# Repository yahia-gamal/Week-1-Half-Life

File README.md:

First, some files are called star, as i intended to make starbie but changed my opinion.

Second, i did a very bad mistake by building up the time until i got to work on this project for 6 hours in a single day and it wasn't the best experience. Luckily, i knew how to deal with KiCad but later on, i won't be able to deal with CADing.

First thing i did in that project was following the project without changing anything 
Those are photos of what i have done.

I followed the tutorial and made the whole star in about 2-2.5 hours
After having some rest, i continued on this project but decided to continue with a bunny instead of star because why not (Idk the reason tbh)

After spending 3 hours on fixing bugs and adding other circuits (I only added LDR and haptic motor), I finished with those. And i admit they were so impressive and i was proud

Spent the rest of the time preparing the code by adding some conditions like forcing sleeping when there is no to little amount of light using LDR and followed the rest of the tutorial. In addition, i added my rabbit pet instead of the pet that was provided in the tutorial.
Finally, i set up github to publish this and future projects.
(i know git was supposed to be done first, but it is what it is)

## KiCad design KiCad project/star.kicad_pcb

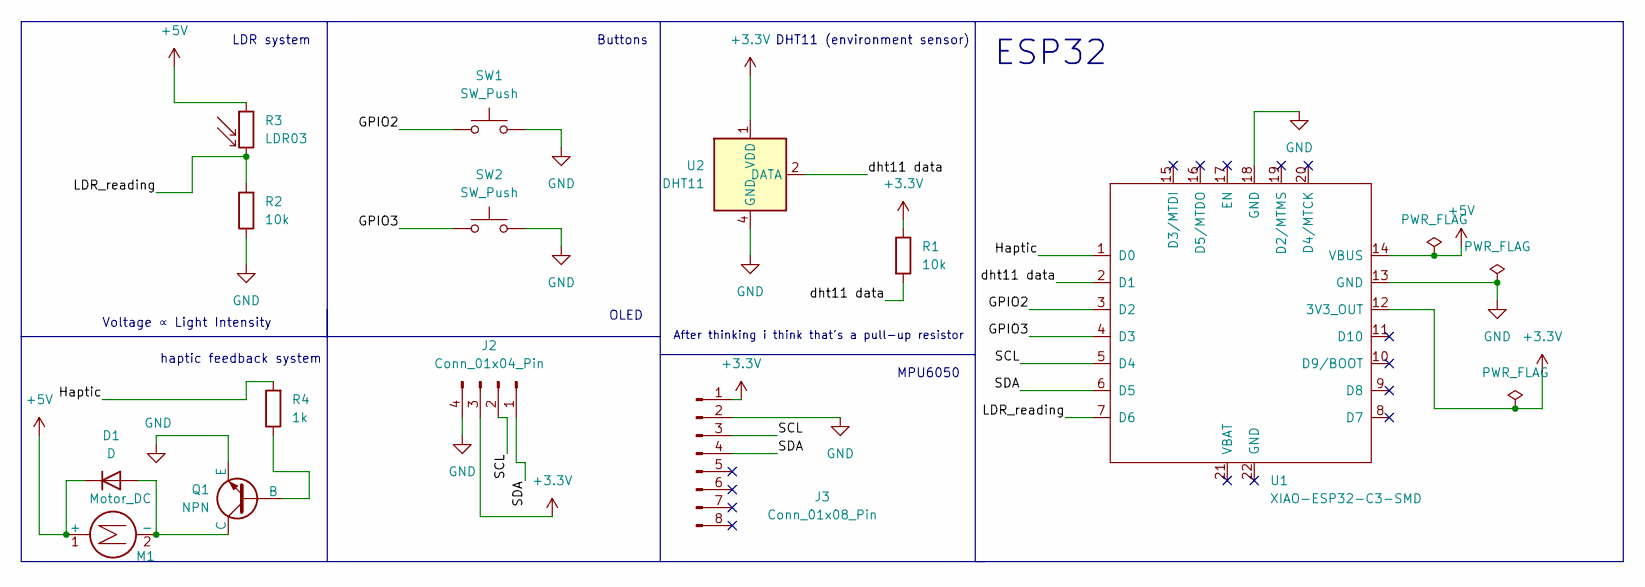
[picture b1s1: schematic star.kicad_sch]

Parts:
D1: D; D_T-1_P10.16mm_Horizontal
J2: Conn_01x04_Pin; Display_128x64_096_I2C
J3: Conn_01x08_Pin; PinHeader_1x08_P2.54mm_Vertical
M1: Motor_DC; Untitled
Q1: NPN; TO-92_Inline
R1, R2: 10k; R_Axial_DIN0204_L3.6mm_D1.6mm_P7.62mm_Horizontal
R3: LDR03; R_LDR_10x8.5mm_P7.6mm_Vertical
R4: 1k; R_Axial_DIN0204_L3.6mm_D1.6mm_P7.62mm_Horizontal
SW1, SW2: SW_Push; SW_Cherry_MX_1.00u_PCB
U1: XIAO-ESP32-C3-SMD
U2: DHT11; Aosong_DHT11_5.5x12.0_P2.54mm

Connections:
+3.3V: J2.3, J3.1, R1.1, U1.12 (3V3_OUT), U2.1 (VDD)
+5V: D1.1 (K), M1.1 (+), R3.1, U1.14 (VBUS)
/GPIO2: SW1.1, U1.3 (D2)
/GPIO3: SW2.1, U1.4 (D3)
/Haptic: R4.2, U1.1 (D0)
/LDR_reading: R2.2, R3.2, U1.7 (D6)
/SCL: J2.2, J3.3, U1.5 (D4)
/SDA: J2.1, J3.4, U1.6 (D5)
/dht11 data: R1.2, U1.2 (D1), U2.2 (DATA)
GND: J2.4, J3.2, Q1.3 (E), R2.1, SW1.2, SW2.2, U1.13 (GND), U1.18 (GND), U2.4 (GND)
unnamed: D1.2 (A), M1.2 (-), Q1.1 (C)
unnamed: Q1.2 (B), R4.1

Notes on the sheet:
LDR system
Buttons
haptic feedback system
DHT11 (environment sensor)
After thinking i think that's a pull-up resistor
MPU6050
Voltage ∝ Light Intensity
ESP32
OLED

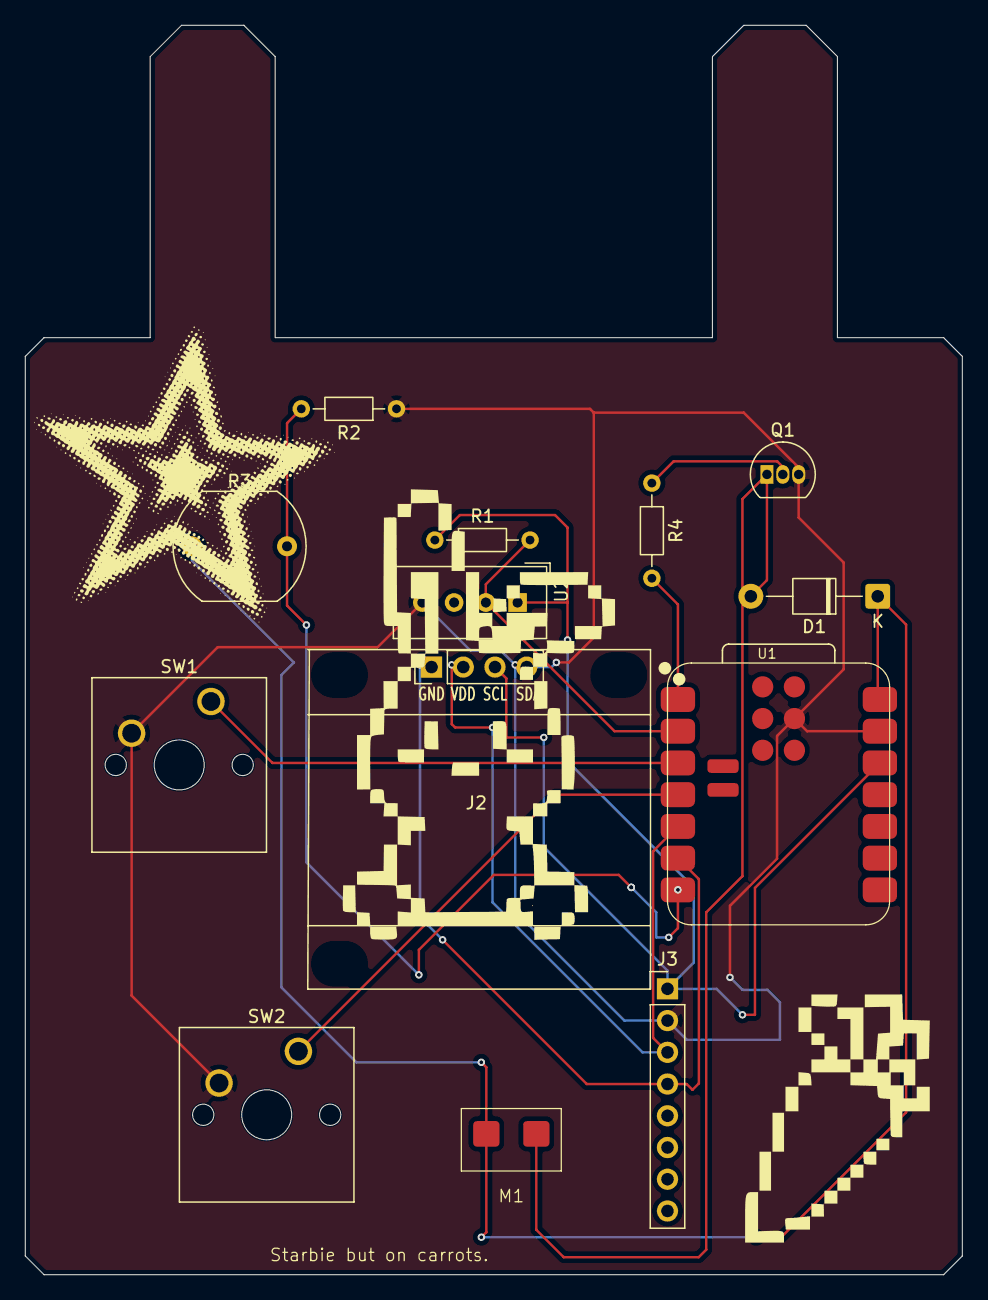
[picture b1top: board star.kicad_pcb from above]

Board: 2 copper layers, 75.0 x 100.0 mm, 13 parts (0 on the bottom side), 12 nets.

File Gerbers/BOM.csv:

Ref,Val,Package,PosX,PosY,Rot,Side
"D1","D","D_T-1_P10.16mm_Horizontal",165.730000,-115.700000,180.000000,top
"J2","Conn_01x04_Pin","Display_128x64_096_I2C",133.824000,-121.365000,0.000000,top
"J3","Conn_01x08_Pin","PinHeader_1x08_P2.54mm_Vertical",148.900000,-147.120000,0.000000,top
"M1","Motor_DC","Untitled",136.400000,-158.700000,0.000000,top
"Q1","NPN","TO-92_Inline",156.860000,-105.950000,0.000000,top
"R1","10k","R_Axial_DIN0204_L3.6mm_D1.6mm_P7.62mm_Horizontal",130.280000,-111.200000,0.000000,top
"R2","10k","R_Axial_DIN0204_L3.6mm_D1.6mm_P7.62mm_Horizontal",127.210000,-100.700000,180.000000,top
"R3","LDR03","R_LDR_10x8.5mm_P7.6mm_Vertical",110.850000,-111.700000,0.000000,top
"R4","1k","R_Axial_DIN0204_L3.6mm_D1.6mm_P7.62mm_Horizontal",147.650000,-106.640000,-90.000000,top
"SW1","SW_Push","SW_Cherry_MX_1.00u_PCB",112.360000,-124.120000,0.000000,top
"SW2","SW_Push","SW_Cherry_MX_1.00u_PCB",119.360000,-152.120000,0.000000,top
"U1","XIAO-ESP32-C3-SMD","XIAO-ESP32-C3-SMD",148.900000,-142.080000,0.000000,top
"U2","DHT11","Aosong_DHT11_5.5x12.0_P2.54mm",136.900000,-116.200000,-90.000000,top
